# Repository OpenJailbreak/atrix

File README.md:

# Atrix v1.0.2
Atrix is an open source project based around iPhone/iPad/iPod 30pin to serial adapter or breakout hardware.

Two subprojects exsist;

Atrix half breakout - just gives you a small piece of hardware that just breaks out USB for sync and serial for uses such as on device kernel debugging. This is more of a BYOB (bring your own board) project as you'll need to provide your own serial converter such as an FTDI Basic, or the similar. 

Atrix full breakout (TODO) - gives you all 30 pins broken out just like a PodBreakout would.  

Atrix adapter - gives you everything you need in one package, FTDI and USB all on one board for convenience.

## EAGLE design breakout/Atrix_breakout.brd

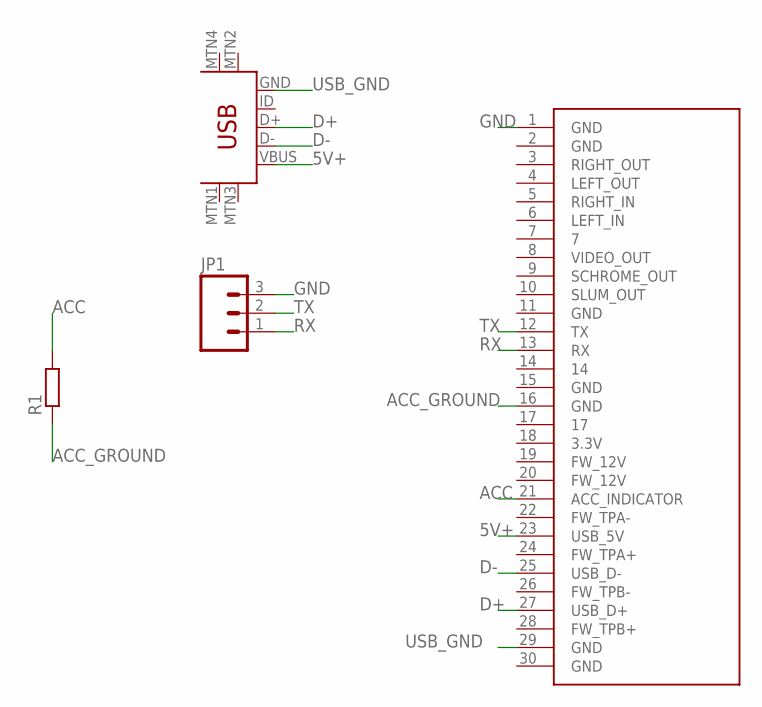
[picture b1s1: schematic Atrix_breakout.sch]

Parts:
JP1: M03; 03P
R1: R0207/10; 0207/10
U$1: IPOD_CONNECTOR_MALE; IPOD_MALE_CONNECTOR
U$3: USB-MINIB-5PIN; USB-MINIB

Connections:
5V+: U$1.23 (USB_5V), U$3.VBUS
ACC: R1.2, U$1.21 (ACC_INDICATOR)
ACC_GROUND: R1.1, U$1.16 (GND)
D+: U$1.27 (USB_D+), U$3.D+
D-: U$1.25 (USB_D-), U$3.D-
GND: JP1.3, U$1.1 (GND)
RX: JP1.1, U$1.13 (RX)
TX: JP1.2, U$1.12 (TX)
USB_GND: U$1.29 (GND), U$3.GND

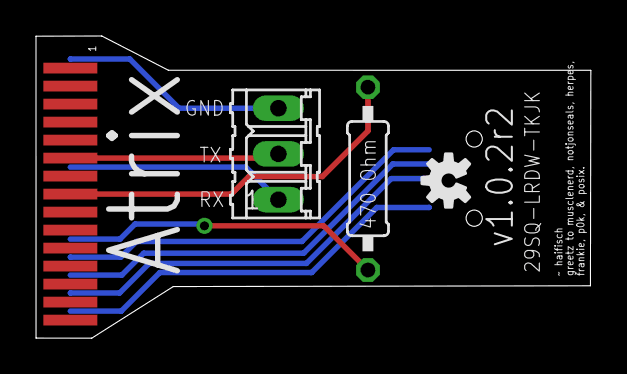
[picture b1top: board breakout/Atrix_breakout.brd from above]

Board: 2 copper layers, 30.8 x 16.8 mm, 5 parts (1 on the bottom side), 9 nets.

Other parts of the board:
U$2: OSHW-LOGO-S

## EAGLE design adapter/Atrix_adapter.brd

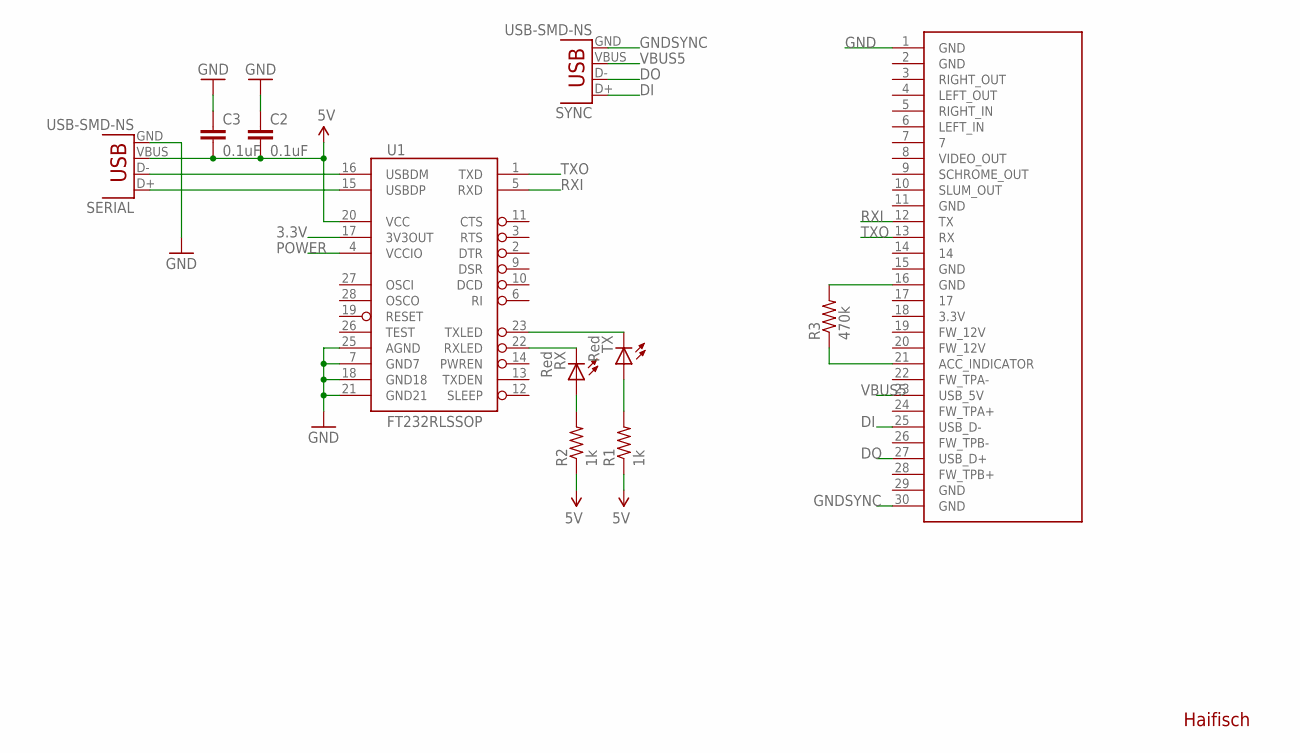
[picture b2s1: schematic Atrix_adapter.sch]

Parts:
C2, C3: 0.1uF; 0402-CAP
R1, R2: 1k; 0402-RES
R3: 470k; 0402-RES
RX: Red; CHIP-LED0603
SERIAL: USB-SMD-NS; USB-MINIB-NOSTOP
SYNC: USB-SMD-NS; USB-MINIB-NOSTOP
TX: Red; CHIP-LED0603
U1: FT232RLSSOP; SSOP28DB
U$1: IPOD_CONNECTOR_MALE; IPOD_MALE_CONNECTOR

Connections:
3.3V: U1.17 (3V3OUT)
5V: C2.2, C3.2, R1.1, R2.1, SERIAL.VBUS, U1.20 (VCC)
DI: SYNC.D+, U$1.25 (USB_D-)
DO: SYNC.D-, U$1.27 (USB_D+)
GND: C2.1, C3.1, SERIAL.GND, U1.7 (GND7), U1.18 (GND18), U1.21 (GND21), U1.25 (AGND), U$1.1 (GND)
GNDSYNC: SYNC.GND, U$1.30 (GND)
unnamed: R3.1, U$1.21 (ACC_INDICATOR)
unnamed: R3.2, U$1.16 (GND)
unnamed: SERIAL.D+, U1.15 (USBDP)
unnamed: SERIAL.D-, U1.16 (USBDM)
unnamed: R2.2, RX.A
unnamed: R1.2, TX.A
POWER: U1.4 (VCCIO)
RXI: U1.5 (RXD), U$1.12 (TX)
RXLED: RX.C, U1.22 (RXLED)
TXLED: TX.C, U1.23 (TXLED)
TXO: U1.1 (TXD), U$1.13 (RX)
VBUS5: SYNC.VBUS, U$1.23 (USB_5V)

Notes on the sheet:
Haifisch

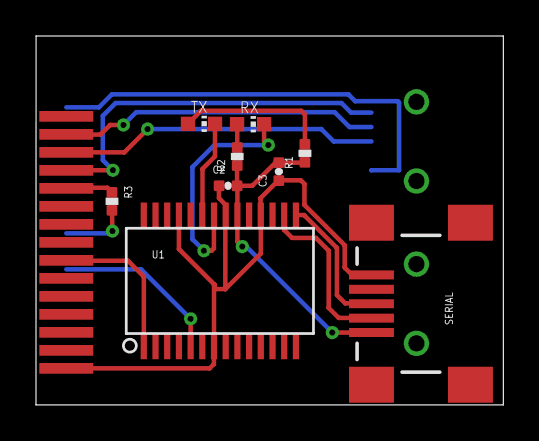
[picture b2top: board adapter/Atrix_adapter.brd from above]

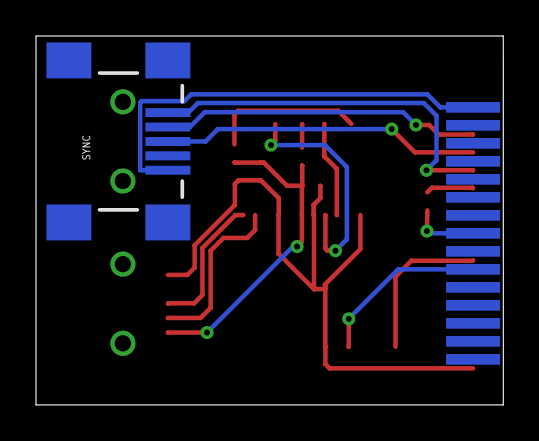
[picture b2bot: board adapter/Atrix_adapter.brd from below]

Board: 2 copper layers, 26.0 x 20.5 mm, 11 parts (2 on the bottom side), 16 nets.

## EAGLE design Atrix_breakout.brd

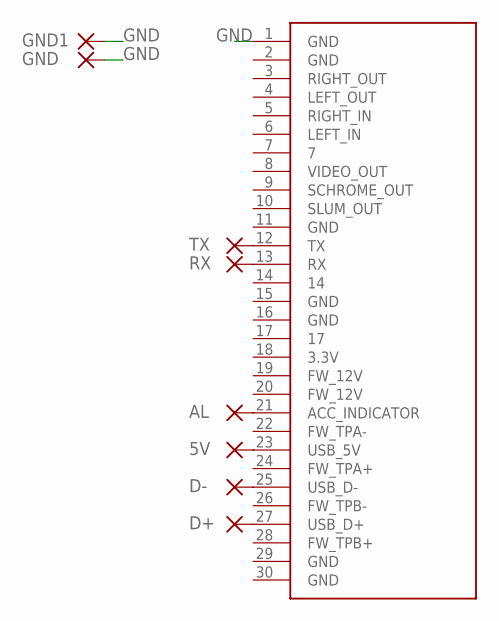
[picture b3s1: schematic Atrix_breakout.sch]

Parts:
5V: 1,6/0,8
AL: 1,6/0,8
D+: 1,6/0,8
D-: 1,6/0,8
GND, GND1: 1,6/0,8
RX: 1,6/0,8
TX: 1,6/0,8
U$1: IPOD_CONNECTOR_MALE; IPOD_MALE_CONNECTOR

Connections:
GND: GND.1, GND1.1, U$1.1 (GND)
unnamed: AL.1, U$1.21 (ACC_INDICATOR)
unnamed: D-.1, U$1.25 (USB_D-)
unnamed: D+.1, U$1.27 (USB_D+)
unnamed: RX.1, U$1.13 (RX)
unnamed: TX.1, U$1.12 (TX)
unnamed: 5V.1, U$1.23 (USB_5V)

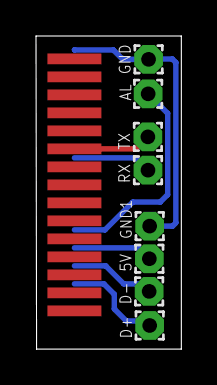
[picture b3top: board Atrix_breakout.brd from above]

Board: 2 copper layers, 8.1 x 17.4 mm, 9 parts (0 on the bottom side), 7 nets.

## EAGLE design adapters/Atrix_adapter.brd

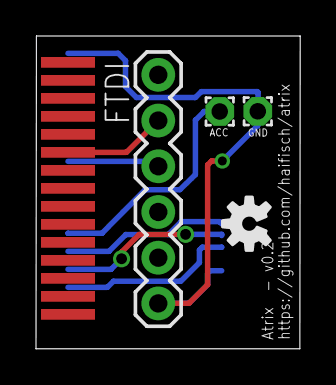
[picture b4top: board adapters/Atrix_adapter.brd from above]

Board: 2 copper layers, 14.7 x 17.4 mm, 6 parts (1 on the bottom side), 7 nets.

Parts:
ACC: 1,6/0,9
GND: 1,6/0,9
JP1: FTDI; FTDI_BASIC
U$1: IPOD_CONNECTOR_MALE; IPOD_MALE_CONNECTOR
U$2: OSHW-LOGO-S
X1: USB-MICROB

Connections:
5V: U$1.23, X1.VBUS
D+: U$1.27, X1.D+
D-: U$1.25, X1.D-
GND: GND.1, JP1.GND, U$1.1, X1.GND
unnamed: ACC.1, U$1.21
RX: JP1.TXO, U$1.13
TX: JP1.RXI, U$1.12

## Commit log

2015-03-11 Change license to CERN OHL, Push eagle files
2015-03-11 Update README with How-to
2015-03-11 Remove unused index file.
2015-03-11 Forgot a step.
2015-03-11 I lost track
2015-03-11 Correct AL pin name, should be ACC
2015-04-03 Push to OpenJB
2015-04-03 Move stuff around, update readme a bit
2015-04-03 Push current adapter board, create mockup, update readme a little
2015-06-13 Breakout updated to v1.0.1, improved board. See rev.txt
2015-08-23 Rev v1.0.2r2
2015-08-23 Add atrix labeling, improve existing serial labeling.

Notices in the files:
parts and their libraries:
SparkFun-Connectors: Licensing: Creative Commons ShareAlike 4.0 International - https://creativecommons.org/licenses/by-sa/4.0
